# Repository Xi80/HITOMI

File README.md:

# HiT0M1-32

Hardware MIDI Tone Generator Machine - 32

***THIS PROJECT HAS BEEN DISCONTINUED!***

## 仕様

メインMCU:**STM32F303K8 UpTo 72MHz**

PSG音源IC:**YMZ294**

FM音源IC:**YM2413**

最大同時発音数:**PSG6和音,FMメロディー24ch,FMリズム5ch**

入力:**MIDI**

I/F:**USB(UART@9600bps),MIDI(DIN5Pin),3.5mmステレオジャック(出力はモノラル)**

インジケータ:**LEDx1(MIDI IN)**

基板:**100x100,2層**

## ハードウェアについて

回路図を以下に示す。

### Main Board(HiTOMI-32)

### Sub Board(Hikaru)

## ソフトウェア

### 実装した機能

- 30音(メロディー)同時発音可能

- GM1相当の音色マップの一部
- コントロールチェンジ
  - エクスプレッション
  - ボリュームコントロール
- ノートオンイベント
- ノートオフイベント

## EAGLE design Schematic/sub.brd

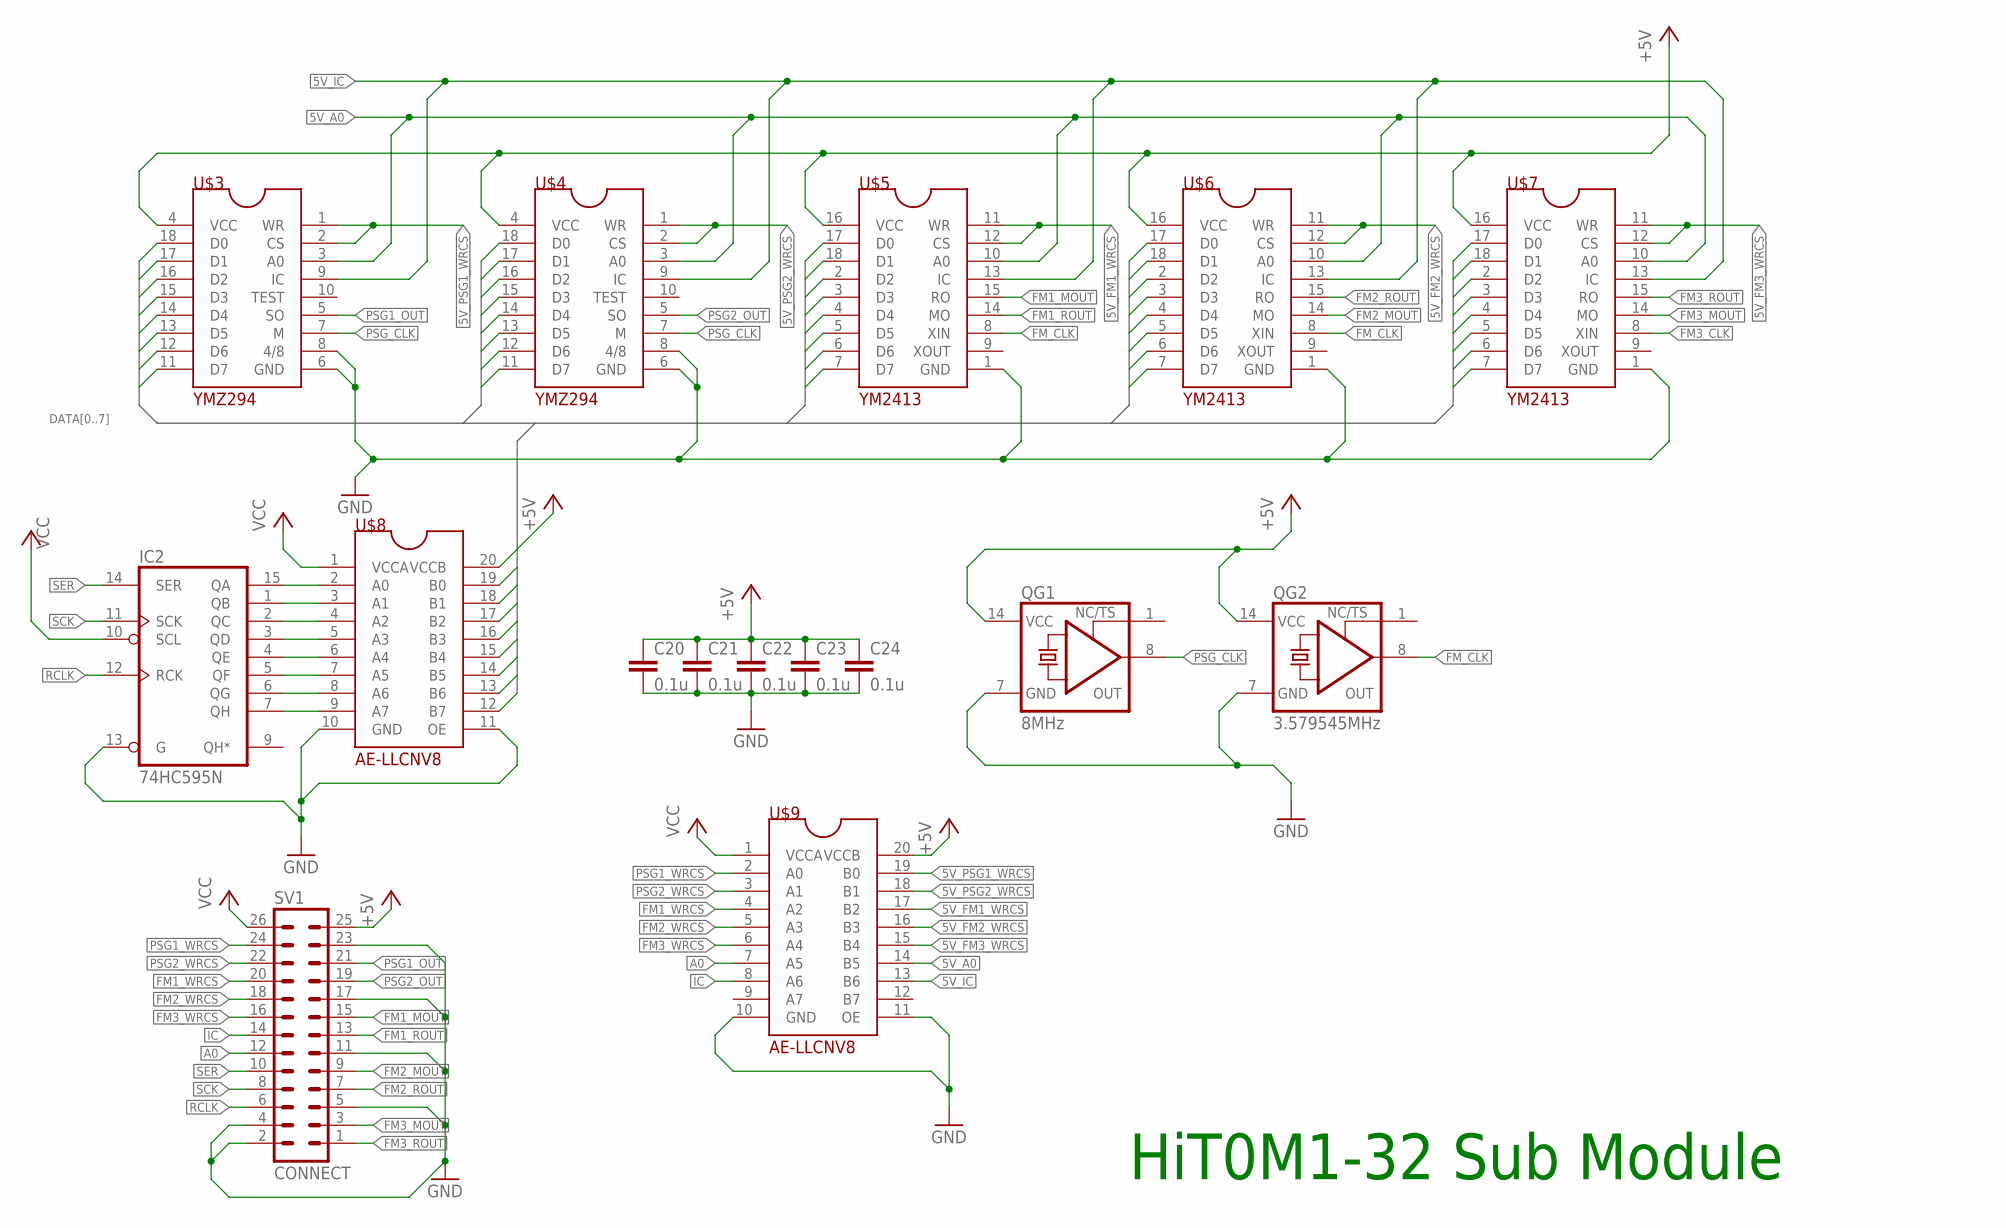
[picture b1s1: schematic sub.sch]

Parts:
C20, C21, C22, C23, C24: 0.1u; C025-025X050
IC2: 74HC595N; DIL16
QG1: 8MHz; DIL14S
QG2: 3.579545MHz; DIL14S
SV1: CONNECT; MA13-2
U$3, U$4: YMZ294; DIL18
U$5, U$6, U$7: YM2413; DIL18
U$8, U$9: AE-LLCNV8; DIL20

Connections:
5V_A0: U$3.3 (A0), U$4.3 (A0), U$5.10 (A0), U$6.10 (A0), U$7.10 (A0), U$9.14 (B5)
5V_FM1_WRCS: U$5.11 (WR), U$5.12 (CS), U$9.17 (B2)
5V_FM2_WRCS: U$6.11 (WR), U$6.12 (CS), U$9.16 (B3)
5V_FM3_WRCS: U$7.11 (WR), U$7.12 (CS), U$9.15 (B4)
5V_IC: U$3.9 (IC), U$4.9 (IC), U$5.13 (IC), U$6.13 (IC), U$7.13 (IC), U$9.13 (B6)
5V_PSG1_WRCS: U$3.1 (WR), U$3.2 (CS), U$9.19 (B0)
5V_PSG2_WRCS: U$4.1 (WR), U$4.2 (CS), U$9.18 (B1)
+5V: C20.1, C21.1, C22.1, C23.1, C24.1, QG1.14 (VCC), QG2.14 (VCC), SV1.25, U$3.4 (VCC), U$4.4 (VCC), U$5.16 (VCC), U$6.16 (VCC), U$7.16 (VCC), U$8.20 (VCCB), U$9.20 (VCCB)
A0: SV1.12, U$9.7 (A5)
DATA0: U$3.18 (D0), U$4.18 (D0), U$5.17 (D0), U$6.17 (D0), U$7.17 (D0), U$8.19 (B0)
DATA1: U$3.17 (D1), U$4.17 (D1), U$5.18 (D1), U$6.18 (D1), U$7.18 (D1), U$8.18 (B1)
DATA2: U$3.16 (D2), U$4.16 (D2), U$5.2 (D2), U$6.2 (D2), U$7.2 (D2), U$8.17 (B2)
DATA3: U$3.15 (D3), U$4.15 (D3), U$5.3 (D3), U$6.3 (D3), U$7.3 (D3), U$8.16 (B3)
DATA4: U$3.14 (D4), U$4.14 (D4), U$5.4 (D4), U$6.4 (D4), U$7.4 (D4), U$8.15 (B4)
DATA5: U$3.13 (D5), U$4.13 (D5), U$5.5 (D5), U$6.5 (D5), U$7.5 (D5), U$8.14 (B5)
DATA6: U$3.12 (D6), U$4.12 (D6), U$5.6 (D6), U$6.6 (D6), U$7.6 (D6), U$8.13 (B6)
DATA7: U$3.11 (D7), U$4.11 (D7), U$5.7 (D7), U$6.7 (D7), U$7.7 (D7), U$8.12 (B7)
FM1_MOUT: SV1.15, U$5.15 (RO)
FM1_ROUT: SV1.13, U$5.14 (MO)
FM1_WRCS: SV1.20, U$9.4 (A2)
FM2_MOUT: SV1.9, U$6.14 (MO)
FM2_ROUT: SV1.7, U$6.15 (RO)
FM2_WRCS: SV1.18, U$9.5 (A3)
FM3_CLK: U$7.8 (XIN)
FM3_MOUT: SV1.3, U$7.14 (MO)
FM3_ROUT: SV1.1, U$7.15 (RO)
FM3_WRCS: SV1.16, U$9.6 (A4)
FM_CLK: QG2.8 (OUT), U$5.8 (XIN), U$6.8 (XIN)
GND: C20.2, C21.2, C22.2, C23.2, C24.2, IC2.8 (GND), IC2.13 (G), QG1.7 (GND), QG2.7 (GND), SV1.2, SV1.4, SV1.5, SV1.11, SV1.17, SV1.23, U$3.6 (GND), U$3.8 (4/8), U$4.6 (GND), U$4.8 (4/8), U$5.1 (GND), U$6.1 (GND), U$7.1 (GND), U$8.10 (GND), U$8.11 (OE), U$9.10 (GND), U$9.11 (OE)
IC: SV1.14, U$9.8 (A6)
unnamed: IC2.15 (QA), U$8.2 (A0)
unnamed: IC2.1 (QB), U$8.3 (A1)
unnamed: IC2.2 (QC), U$8.4 (A2)
unnamed: IC2.4 (QE), U$8.6 (A4)
unnamed: IC2.3 (QD), U$8.5 (A3)
unnamed: IC2.5 (QF), U$8.7 (A5)
unnamed: IC2.6 (QG), U$8.8 (A6)
unnamed: IC2.7 (QH), U$8.9 (A7)
PSG1_OUT: SV1.21, U$3.5 (SO)
PSG1_WRCS: SV1.24, U$9.2 (A0)
PSG2_OUT: SV1.19, U$4.5 (SO)
PSG2_WRCS: SV1.22, U$9.3 (A1)
PSG_CLK: QG1.8 (OUT), U$3.7 (M), U$4.7 (M)
RCLK: IC2.12 (RCK), SV1.6
SCK: IC2.11 (SCK), SV1.8
SER: IC2.14 (SER), SV1.10
VCC: IC2.10 (SCL), IC2.16 (VCC), SV1.26, U$8.1 (VCCA), U$9.1 (VCCA)

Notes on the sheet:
HiT0M1-32 Sub Module

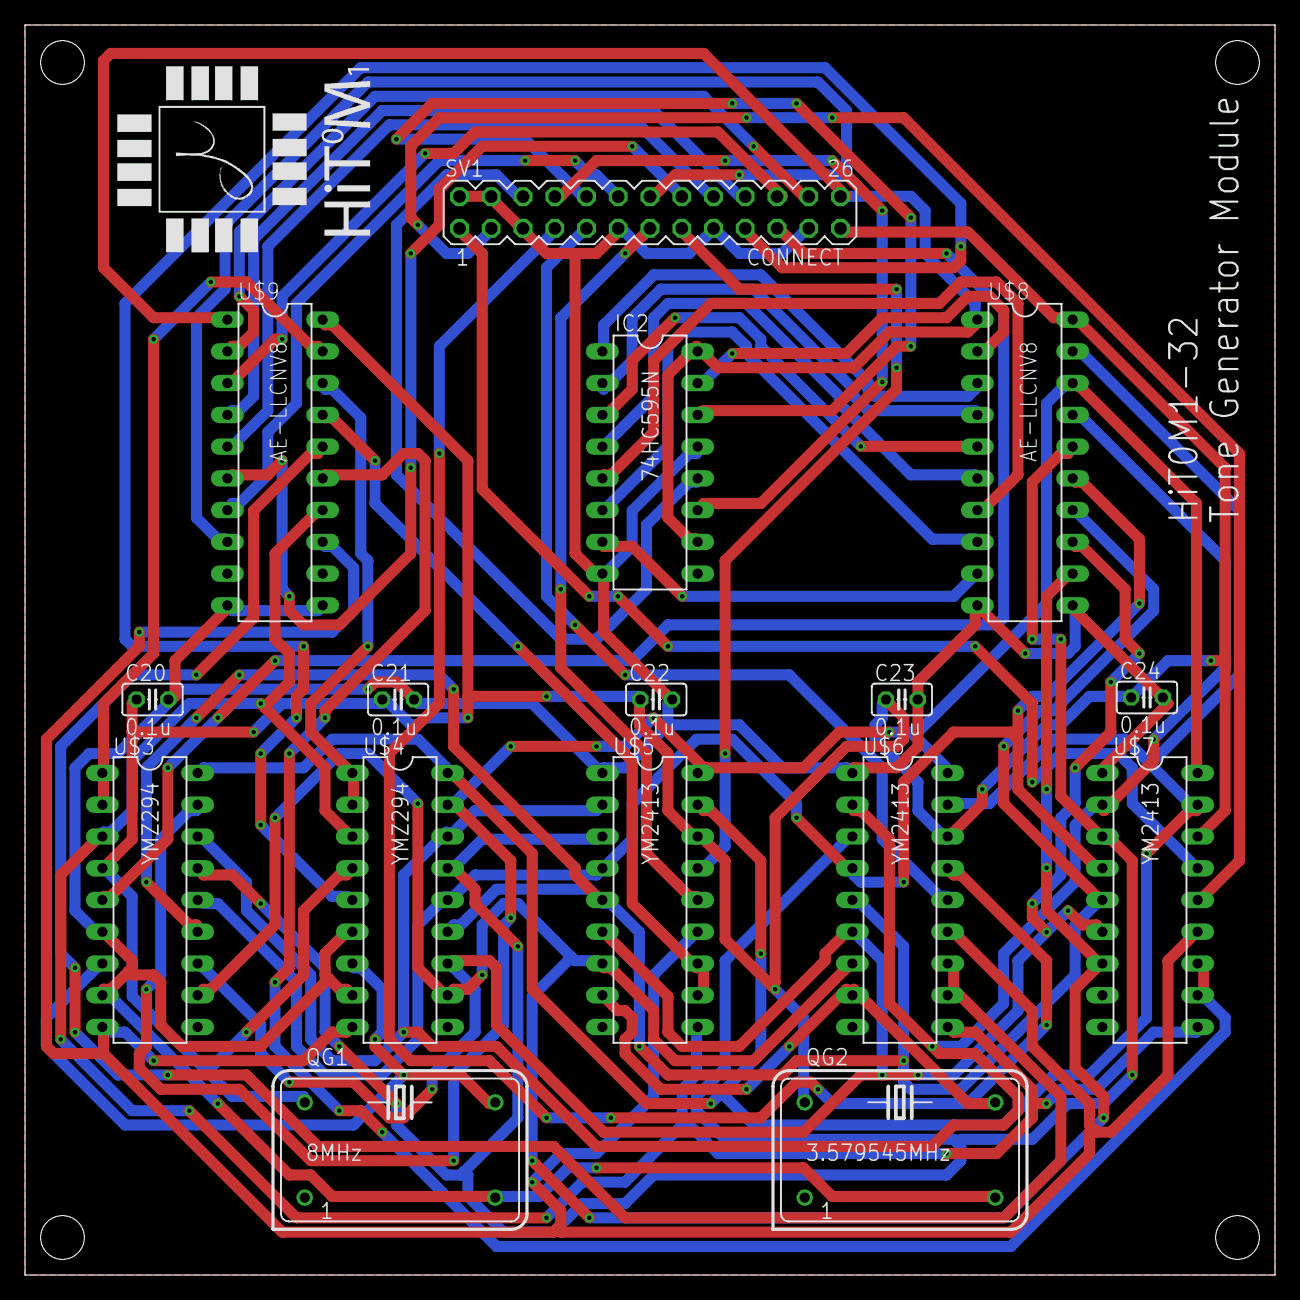
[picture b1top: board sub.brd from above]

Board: 2 copper layers, 100.0 x 100.0 mm, 16 parts (0 on the bottom side), 46 nets.

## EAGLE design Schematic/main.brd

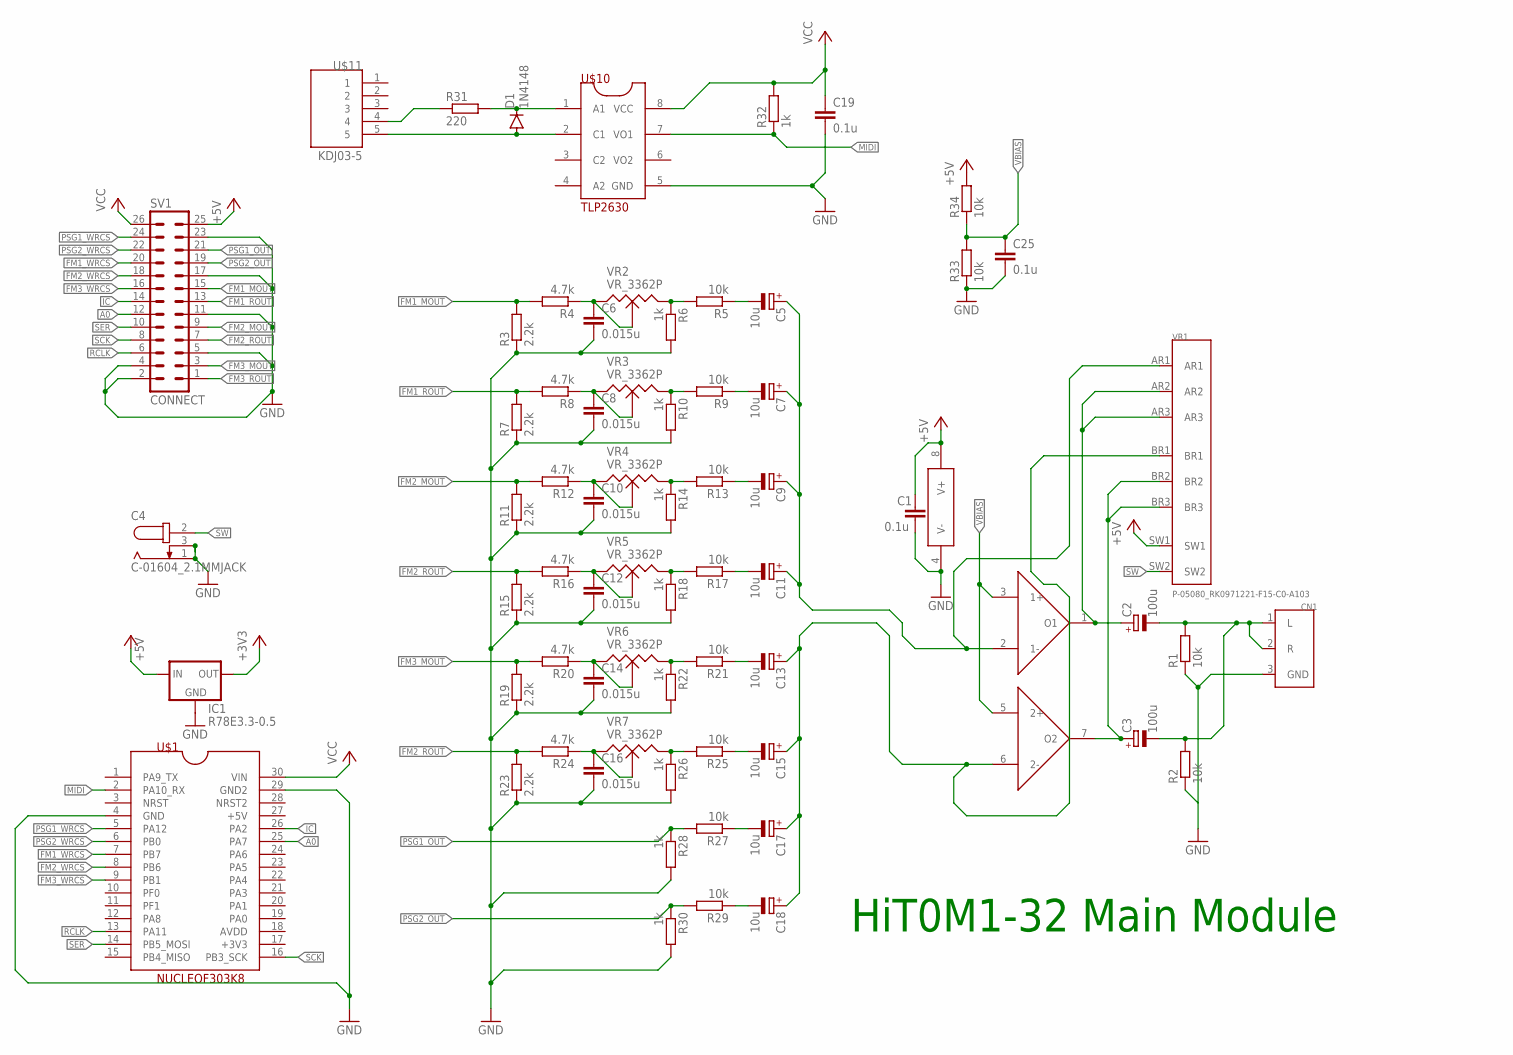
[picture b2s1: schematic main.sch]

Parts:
C1, C19, C25: 0.1u; C025-025X050
C2, C3: 100u; E2,5-6E
C4: C-01604_2.1MMJACK; 2.1MMJACK
C5, C7, C9, C11, C13, C15, C17, C18: 10u; E2,5-6E
C6, C8, C10, C12, C14, C16: 0.015u; C050-025X075
CN1: C-08958_MJ-352W-0; MJ-352W-0
D1: 1N4148; DO35-7
IC1: R78E3.3-0.5; 78XXS
R1, R2, R5, R9, R13, R17, R21, R25, R27, R29, R33, R34: 10k; 0204/7
R3, R7, R11, R15, R19, R23: 2.2k; 0204/7
R4, R8, R12, R16, R20, R24: 4.7k; 0204/7
R6, R10, R14, R18, R22, R26, R28, R30, R32: 1k; 0204/7
R31: 220; 0204/7
SV1: CONNECT; MA13-2
U$1: NUCLEOF303K8
U$2: NJM2114; DIL08
U$10: TLP2630; DIL08
U$11: KDJ03-5
VR1: P-05080_RK0971221-F15-C0-A103; RK0971221-F15-C0-A103
VR2, VR3, VR4, VR5, VR6, VR7: VR_3362P

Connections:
+3V3: IC1.OUT
+5V: C1.1, IC1.IN, R34.2, SV1.25, U$2.8 (V+), VR1.SW1
A0: SV1.12, U$1.25 (PA7)
FM1_MOUT: R3.2, R4.2, SV1.15
FM1_ROUT: R7.2, R8.2, SV1.13
FM1_WRCS: SV1.20, U$1.7 (PB7)
FM2_MOUT: R11.2, R12.2, SV1.9
FM2_ROUT: R15.2, R16.2, R23.2, R24.2, SV1.7
FM2_WRCS: SV1.18, U$1.8 (PB6)
FM3_MOUT: R19.2, R20.2, SV1.3
FM3_ROUT: SV1.1
FM3_WRCS: SV1.16, U$1.9 (PB1)
GND: C1.2, C4.1 (GND), C4.3 (S), C6.2, C8.2, C10.2, C12.2, C14.2, C16.2, C19.2, C25.2, CN1.3 (GND), IC1.GND, R1.1, R3.1, R6.2, R7.1, R10.2, R11.1, R14.2, R15.1, R18.2, R19.1, R22.2, R23.1, R26.2, R28.2, R30.2, R33.1, SV1.2, SV1.4, SV1.5, SV1.11, SV1.17, SV1.23, U$1.4 (GND), U$1.29 (GND2), U$2.4 (V-), U$10.5 (GND)
IC: SV1.14, U$1.26 (PA2)
MIDI: R32.1, U$1.2 (PA10_RX), U$10.7 (VO1)
MIX_1: C5.+, C7.+, C9.+, C11.+, U$2.2 (1-), VR1.AR1
MIX_2: C13.+, C15.+, C17.+, C18.+, U$2.6 (2-), VR1.BR1
unnamed: D1.C, R31.2, U$10.1 (A1)
unnamed: C2.+, U$2.1 (O1), VR1.AR2, VR1.AR3
unnamed: C3.+, U$2.7 (O2), VR1.BR2, VR1.BR3
unnamed: C8.1, R8.1, VR3.1, VR3.2
unnamed: D1.A, U$10.2 (C1), U$11.5
unnamed: C6.1, R4.1, VR2.1, VR2.2
unnamed: R5.2, R6.1, VR2.3
unnamed: C5.-, R5.1
unnamed: R9.2, R10.1, VR3.3
unnamed: C7.-, R9.1
unnamed: C10.1, R12.1, VR4.1, VR4.2
unnamed: R13.2, R14.1, VR4.3
unnamed: C9.-, R13.1
unnamed: C12.1, R16.1, VR5.1, VR5.2
unnamed: R17.2, R18.1, VR5.3
unnamed: C11.-, R17.1
unnamed: C14.1, R20.1, VR6.1, VR6.2
unnamed: R21.2, R22.1, VR6.3
unnamed: C13.-, R21.1
unnamed: C16.1, R24.1, VR7.1, VR7.2
unnamed: R25.2, R26.1, VR7.3
unnamed: C15.-, R25.1
unnamed: C17.-, R27.1
unnamed: C18.-, R29.1
unnamed: R31.1, U$11.4
OUT: C2.-, C3.-, CN1.1 (L), CN1.2 (R), R1.2, R2.2
PSG1_OUT: R27.2, R28.1, SV1.21
PSG1_WRCS: SV1.24, U$1.5 (PA12)
PSG2_OUT: R29.2, R30.1, SV1.19
PSG2_WRCS: SV1.22, U$1.6 (PB0)
RCLK: SV1.6, U$1.13 (PA11)
SCK: SV1.8, U$1.16 (PB3_SCK)
SER: SV1.10, U$1.14 (PB5_MOSI)
SW: C4.2 (VCC), VR1.SW2
VBIAS: C25.1, R33.2, R34.1, U$2.3 (1+), U$2.5 (2+)
VCC: C19.1, R32.2, SV1.26, U$1.30 (VIN), U$10.8 (VCC)

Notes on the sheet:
HiT0M1-32 Main Module

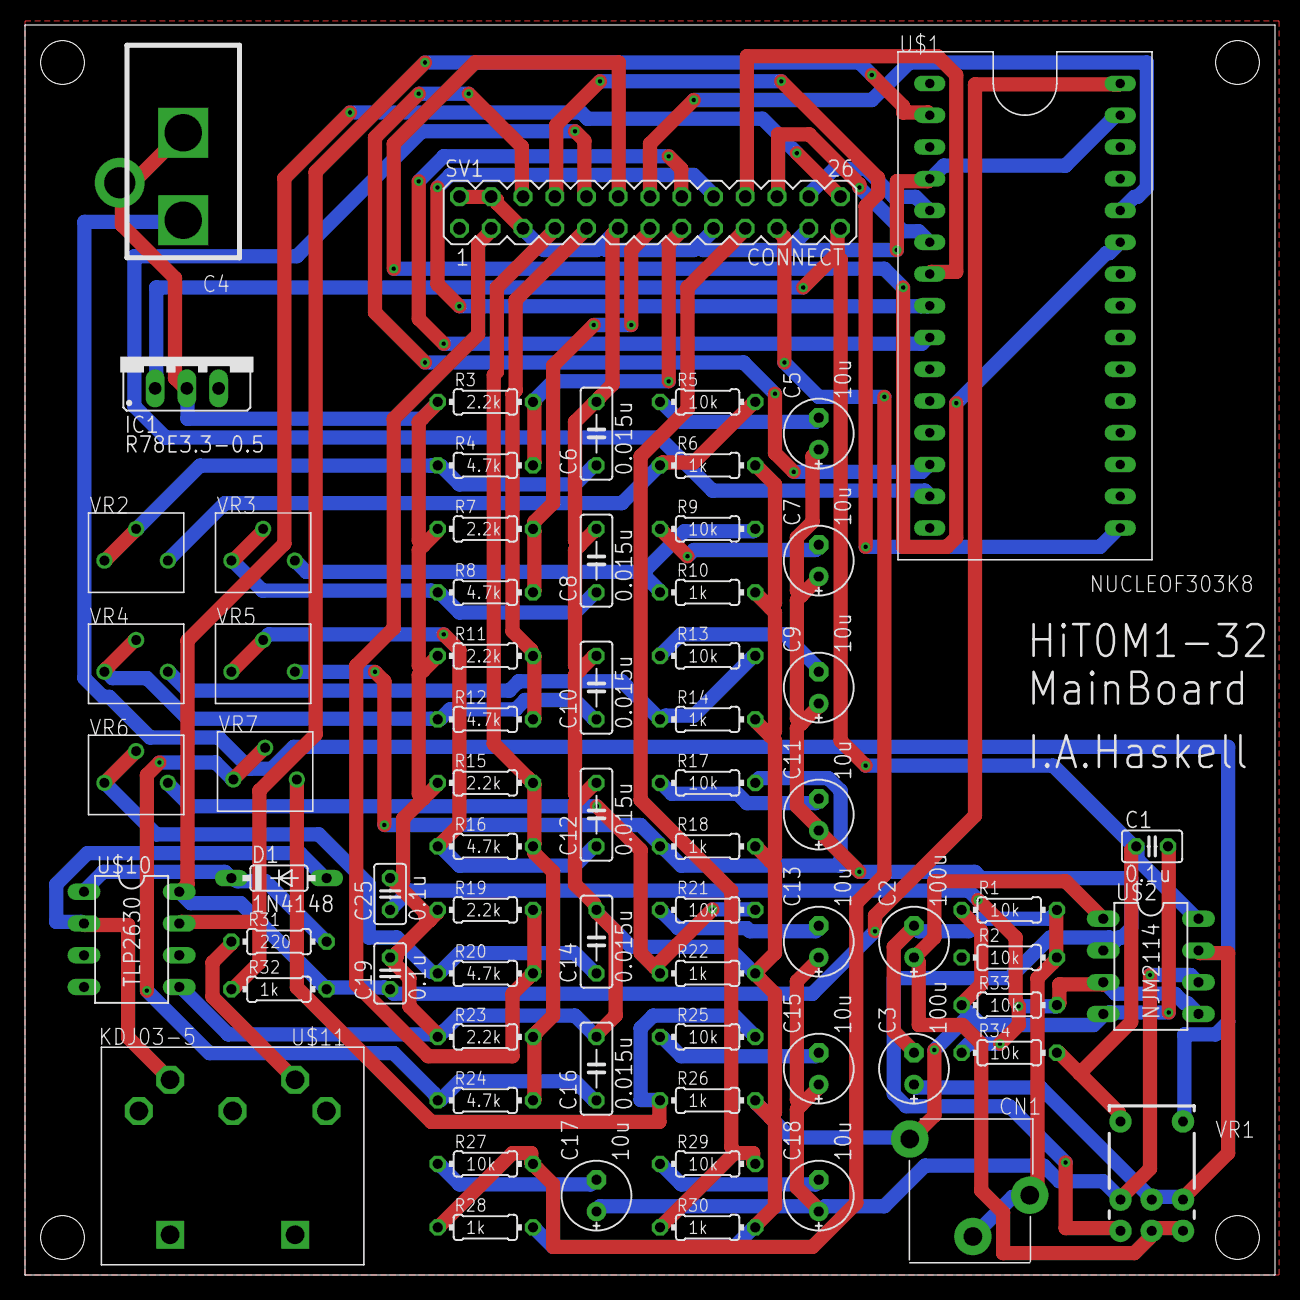
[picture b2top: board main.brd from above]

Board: 2 copper layers, 100.0 x 100.0 mm, 69 parts (0 on the bottom side), 51 nets.

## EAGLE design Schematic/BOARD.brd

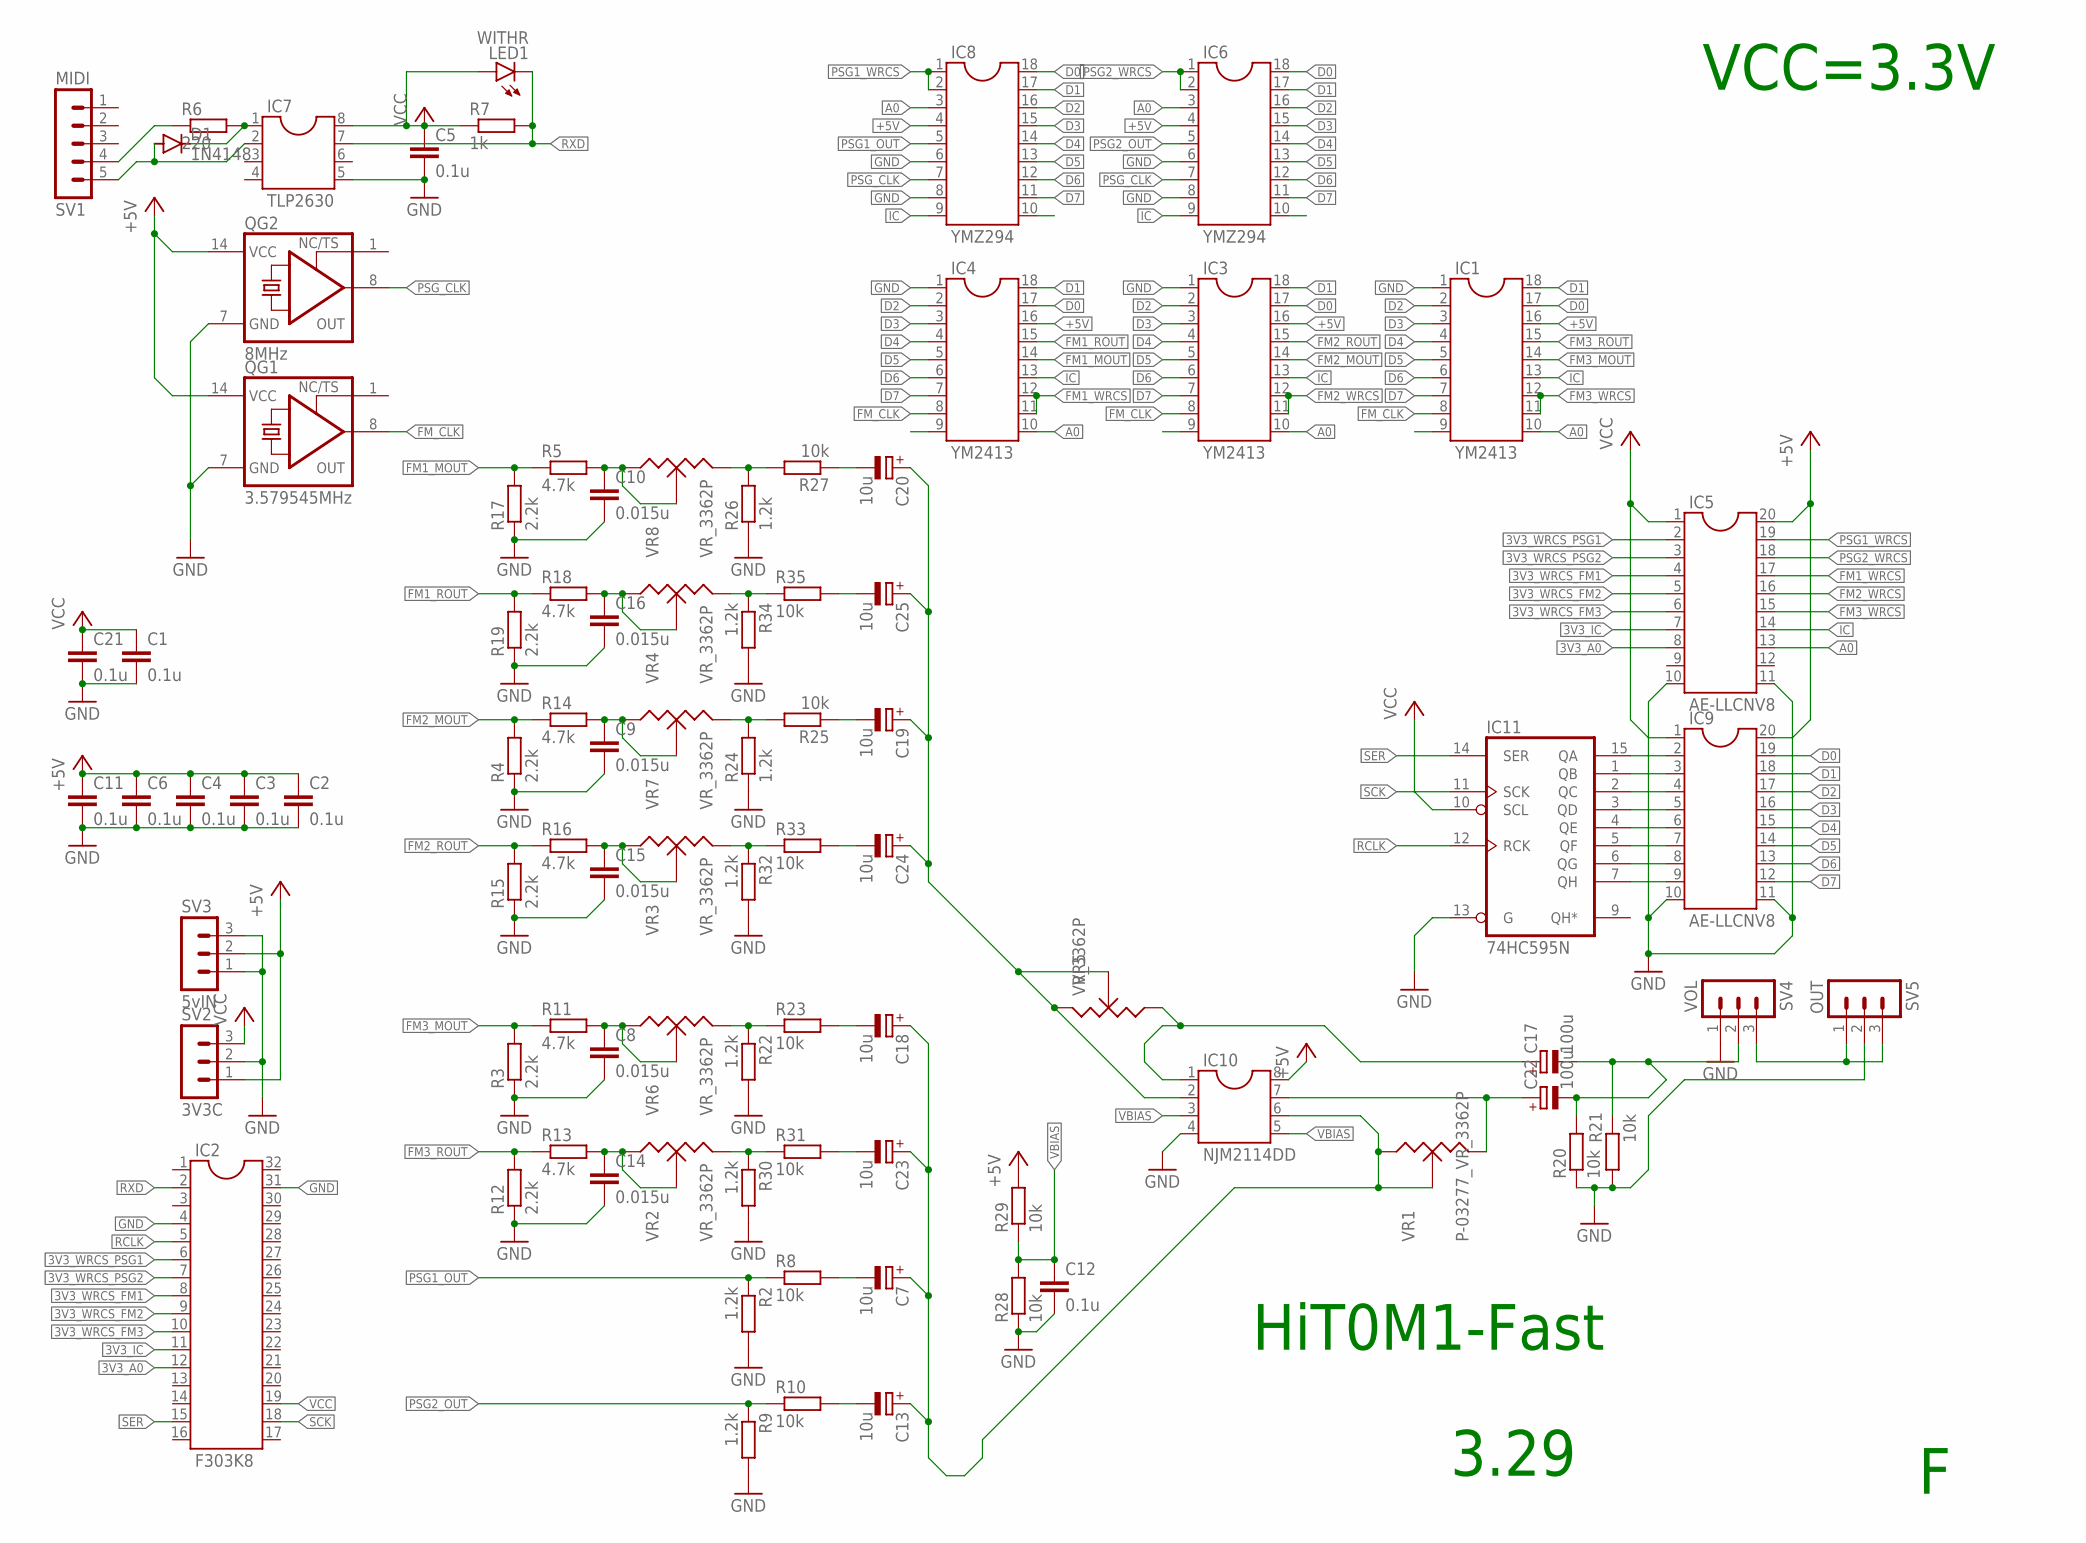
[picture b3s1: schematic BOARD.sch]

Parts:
C1, C2, C3, C4, C5, C6, C11, C12, C21: 0.1u; C025-025X050
C7, C13, C18, C19, C20, C23, C24, C25: 10u; E2,5-6E
C8, C9, C10, C14, C15, C16: 0.015u; C050-025X075
C17, C22: 100u; E2,5-6E
D1: 1N4148; DO35-7
IC1, IC3, IC4: YM2413; SOCKET-18
IC2: F303K8; DIL32
IC5, IC9: AE-LLCNV8; SOCKET-20
IC6, IC8: YMZ294; SOCKET-18
IC7: TLP2630; SOCKET-08
IC10: NJM2114DD; SOCKET-08
IC11: 74HC595N; DIL16
LED1: WITHR; LED3MM
QG1: 3.579545MHz; DIL14S
QG2: 8MHz; DIL14S
R2, R9, R22, R24, R26, R30, R32, R34: 1.2k; 0207/2V
R3, R4, R12, R15, R17, R19: 2.2k; 0207/2V
R5, R11, R13, R14, R16, R18: 4.7k; 0207/2V
R6: 220; 0207/2V
R7: 1k; 0207/2V
R8, R10, R20, R21, R23, R25, R27, R28, R29, R31, R33, R35: 10k; 0207/2V
SV1: MIDI; MA05-1
SV2: 3V3C; MA03-1
SV3: 5vIN; MA03-1
SV4: VOL; MA03-1
SV5: OUT; MA03-1
VR1: P-03277_VR_3362P; VR_3362P
VR2, VR3, VR4, VR5, VR6, VR7, VR8: VR_3362P

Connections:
3V3_A0: IC2.12, IC5.8
3V3_IC: IC2.11, IC5.7
3V3_WRCS_FM1: IC2.8, IC5.4
3V3_WRCS_FM2: IC2.9, IC5.5
3V3_WRCS_FM3: IC2.10, IC5.6
3V3_WRCS_PSG1: IC2.6, IC5.2
3V3_WRCS_PSG2: IC2.7, IC5.3
+5V: C2.1, C3.1, C4.1, C6.1, C11.1, IC1.16, IC3.16, IC4.16, IC5.20, IC6.4, IC8.4, IC9.20, IC10.8, QG1.14 (VCC), QG2.14 (VCC), R29.2, SV2.1, SV3.2
A0: IC1.10, IC3.10, IC4.10, IC5.13, IC6.3, IC8.3
D0: IC1.17, IC3.17, IC4.17, IC6.18, IC8.18, IC9.19
D1: IC1.18, IC3.18, IC4.18, IC6.17, IC8.17, IC9.18
D2: IC1.2, IC3.2, IC4.2, IC6.16, IC8.16, IC9.17
D3: IC1.3, IC3.3, IC4.3, IC6.15, IC8.15, IC9.16
D4: IC1.4, IC3.4, IC4.4, IC6.14, IC8.14, IC9.15
D5: IC1.5, IC3.5, IC4.5, IC6.13, IC8.13, IC9.14
D6: IC1.6, IC3.6, IC4.6, IC6.12, IC8.12, IC9.13
D7: IC1.7, IC3.7, IC4.7, IC6.11, IC8.11, IC9.12
FM1_MOUT: IC4.14, R5.1, R17.2
FM1_ROUT: IC4.15, R18.1, R19.2
FM1_WRCS: IC4.11, IC4.12, IC5.17
FM2_MOUT: IC3.14, R4.2, R14.1
FM2_ROUT: IC3.15, R15.2, R16.1
FM2_WRCS: IC3.11, IC3.12, IC5.16
FM3_MOUT: IC1.14, R3.2, R11.1
FM3_ROUT: IC1.15, R12.2, R13.1
FM3_WRCS: IC1.11, IC1.12, IC5.15
FM_CLK: IC1.8, IC3.8, IC4.8, QG1.8 (OUT)
GND: C1.2, C2.2, C3.2, C4.2, C5.2, C6.2, C8.2, C9.2, C10.2, C11.2, C12.2, C14.2, C15.2, C16.2, C21.2, IC1.1, IC2.4, IC2.31, IC3.1, IC4.1, IC5.10, IC5.11, IC6.6, IC6.8, IC7.5, IC8.6, IC8.8, IC9.10, IC9.11, IC10.4, IC11.8 (GND), IC11.13 (G), QG1.7 (GND), QG2.7 (GND), R2.2, R3.1, R4.1, R9.2, R12.1, R15.1, R17.1, R19.1, R20.1, R21.1, R22.2, R24.1, R26.1, R28.1, R30.2, R32.2, R34.2, SV2.2, SV3.1, SV3.3, SV4.1, SV5.2
IC: IC1.13, IC3.13, IC4.13, IC5.14, IC6.9, IC8.9
unnamed: C10.1, R5.2, VR8.1, VR8.2
unnamed: D1.C, IC7.1, R6.2
unnamed: C16.1, R18.2, VR4.1, VR4.2
unnamed: R6.1, SV1.4
unnamed: IC9.2, IC11.15 (QA)
unnamed: IC9.3, IC11.1 (QB)
unnamed: IC9.4, IC11.2 (QC)
unnamed: IC9.5, IC11.3 (QD)
unnamed: IC9.6, IC11.4 (QE)
unnamed: IC9.7, IC11.5 (QF)
unnamed: IC9.8, IC11.6 (QG)
unnamed: IC9.9, IC11.7 (QH)
unnamed: C9.1, R14.2, VR7.1, VR7.2
unnamed: D1.A, IC7.2, SV1.5
unnamed: C15.1, R16.2, VR3.1, VR3.2
unnamed: C7.+, C13.+, C18.+, C23.+, IC10.6, VR1.1, VR1.2
unnamed: R32.1, R33.1, VR3.3
unnamed: R24.2, R25.2, VR7.3
unnamed: R34.1, R35.1, VR4.3
unnamed: R26.2, R27.2, VR8.3
unnamed: C20.-, R27.1
unnamed: C25.-, R35.2
unnamed: C19.-, R25.1
unnamed: C24.-, R33.2
unnamed: C19.+, C20.+, C24.+, C25.+, IC10.2, VR5.2, VR5.3
unnamed: C8.1, R11.2, VR6.1, VR6.2
unnamed: R22.1, R23.1, VR6.3
unnamed: C18.-, R23.2
unnamed: C14.1, R13.2, VR2.1, VR2.2
unnamed: R30.1, R31.1, VR2.3
unnamed: C23.-, R31.2
unnamed: C7.-, R8.2
unnamed: C13.-, R10.2
unnamed: SV4.3, SV5.1, SV5.3
unnamed: C17.+, IC10.1, VR5.1
unnamed: C22.+, IC10.7, VR1.3
OUT: C17.-, C22.-, R20.2, R21.2, SV4.2
PSG1_OUT: IC8.5, R2.1, R8.1
PSG1_WRCS: IC5.19, IC8.1, IC8.2
PSG2_OUT: IC6.5, R9.1, R10.1
PSG2_WRCS: IC5.18, IC6.1, IC6.2
PSG_CLK: IC6.7, IC8.7, QG2.8 (OUT)
RCLK: IC2.5, IC11.12 (RCK)
RXD: IC2.2, IC7.7, LED1.K (C), R7.2
SCK: IC2.18, IC11.11 (SCK)
SER: IC2.15, IC11.14 (SER)
VBIAS: C12.1, IC10.3, IC10.5, R28.2, R29.1
VCC: C1.1, C5.1, C21.1, IC2.19, IC5.1, IC7.8, IC9.1, IC11.10 (SCL), IC11.16 (VCC), LED1.A, R7.1, SV2.3

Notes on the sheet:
HiT0M1-Fast
VCC=3.3V
3.29

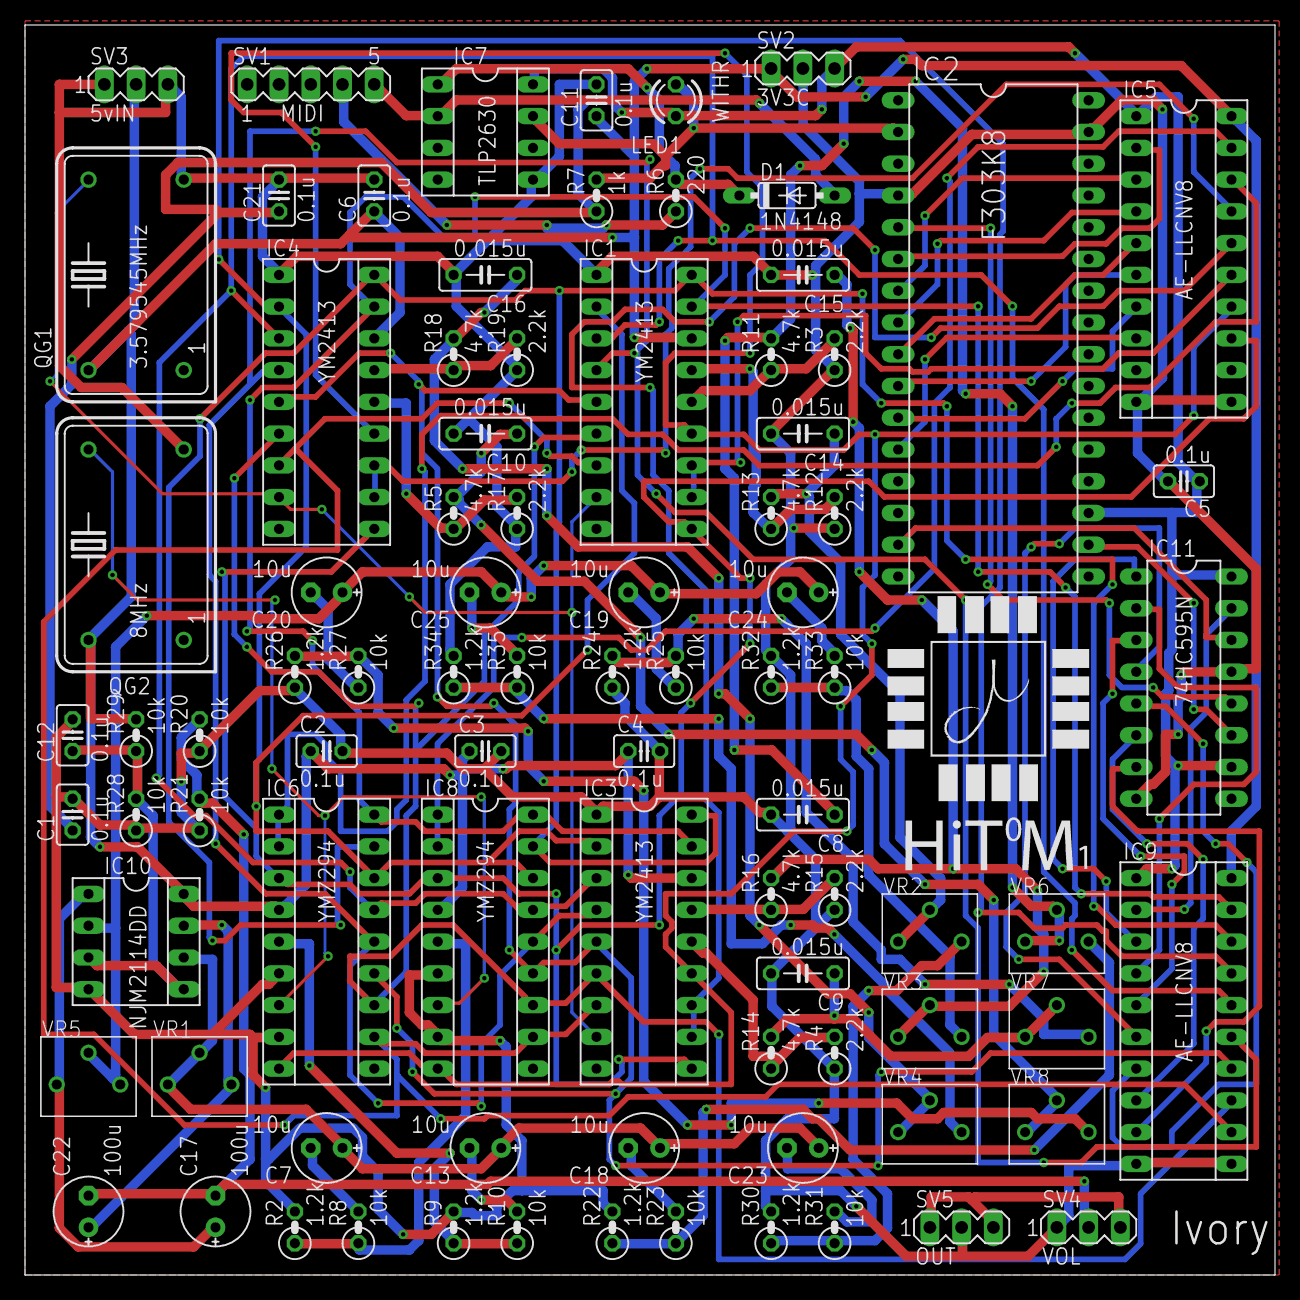
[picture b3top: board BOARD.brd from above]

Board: 2 copper layers, 100.0 x 100.0 mm, 87 parts (0 on the bottom side), 77 nets.

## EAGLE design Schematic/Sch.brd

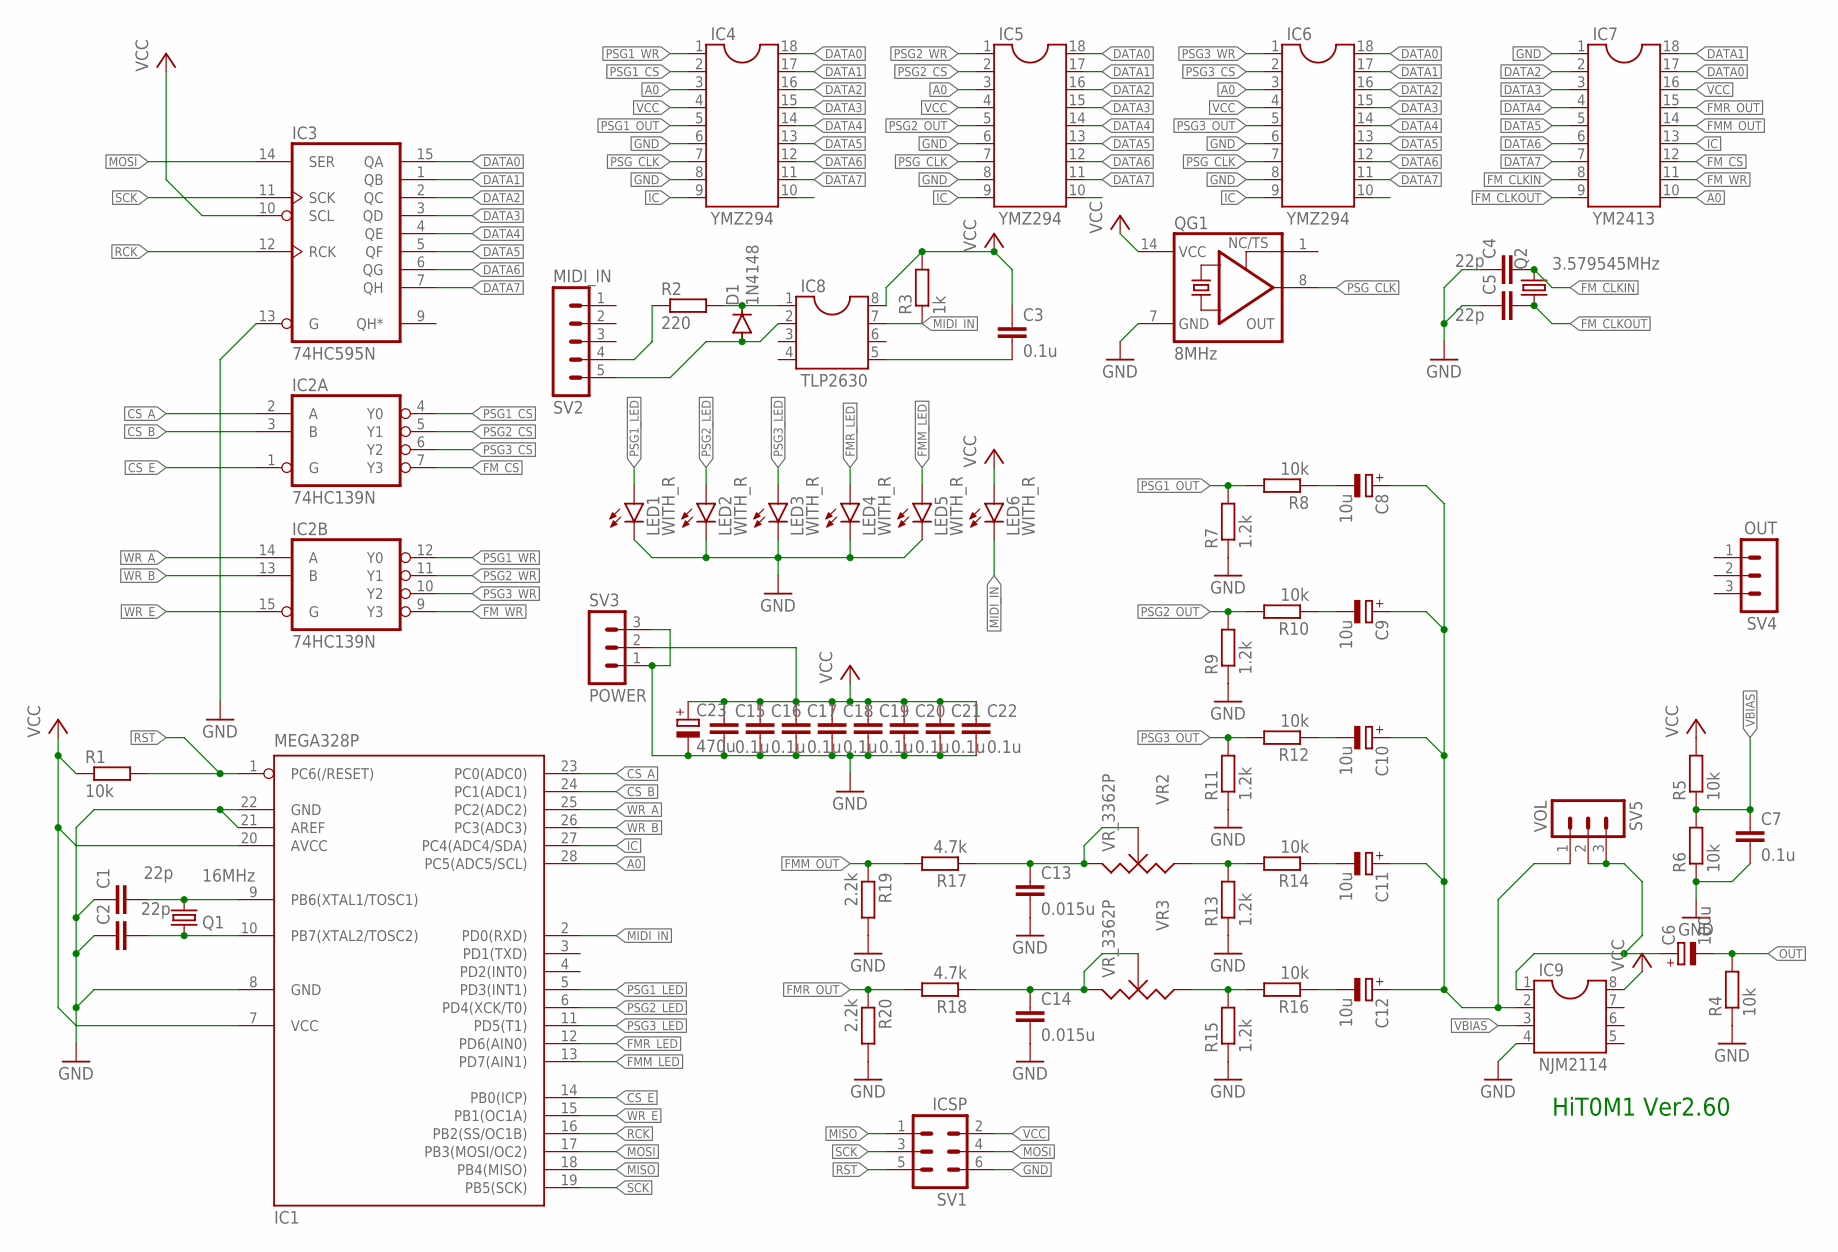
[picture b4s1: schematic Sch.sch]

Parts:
C1, C2, C4, C5: 22p; C025-025X050
C3, C7, C15, C16, C17, C18, C19, C20, C21, C22: 0.1u; C025-025X050
C6: 100u; E2,5-6
C8, C9, C10, C11, C12: 10u; E2,5-6
C13, C14: 0.015u; C050-025X075
C23: 470u; E2,5-6
D1: 1N4148; DO35-7
IC1: MEGA328P; DIL28-3
IC2: 74HC139N; DIL16
IC3: 74HC595N; DIL16
IC4, IC5, IC6: YMZ294; SOCKET-18
IC7: YM2413; SOCKET-18
IC8: TLP2630; SOCKET-08
IC9: NJM2114; SOCKET-08
LED1, LED2, LED3, LED4, LED5, LED6: WITH_R; LED3MM
Q1: 16MHz; HC49/S
Q2: 3.579545MHz; HC49/S
QG1: 8MHz; DIL14S
R1, R4, R5, R6: 10k; 0207/10
R2: 220; 0207/10
R3: 1k; 0207/10
R7, R9, R11, R13, R15: 1.2k; 0207/2V
R8, R10, R12, R14, R16: 10k; 0207/2V
R17, R18: 4.7k; 0207/2V
R19, R20: 2.2k; 0207/2V
SV1: ICSP; MA03-2
SV2: MIDI_IN; MA05-1
SV3: POWER; MA03-1
SV4: OUT; MA03-1
SV5: VOL; MA03-1
VR2, VR3: VR_3362P

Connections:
A0: IC1.28 (PC5(ADC5/SCL)), IC4.3, IC5.3, IC6.3, IC7.10
CS_A: IC1.23 (PC0(ADC0)), IC2.2 (A)
CS_B: IC1.24 (PC1(ADC1)), IC2.3 (B)
CS_E: IC1.14 (PB0(ICP)), IC2.1 (G)
DATA0: IC3.15 (QA), IC4.18, IC5.18, IC6.18, IC7.17
DATA1: IC3.1 (QB), IC4.17, IC5.17, IC6.17, IC7.18
DATA2: IC3.2 (QC), IC4.16, IC5.16, IC6.16, IC7.2
DATA3: IC3.3 (QD), IC4.15, IC5.15, IC6.15, IC7.3
DATA4: IC3.4 (QE), IC4.14, IC5.14, IC6.14, IC7.4
DATA5: IC3.5 (QF), IC4.13, IC5.13, IC6.13, IC7.5
DATA6: IC3.6 (QG), IC4.12, IC5.12, IC6.12, IC7.6
DATA7: IC3.7 (QH), IC4.11, IC5.11, IC6.11, IC7.7
FMM_LED: IC1.13 (PD7(AIN1)), LED5.A
FMM_OUT: IC7.14, R17.2, R19.1
FMR_LED: IC1.12 (PD6(AIN0)), LED4.A
FMR_OUT: IC7.15, R18.2, R20.1
FM_CLKIN: C4.2, IC7.8, Q2.2
FM_CLKOUT: C5.2, IC7.9, Q2.1
FM_CS: IC2.7 (Y3), IC7.12
FM_WR: IC2.9 (Y3), IC7.11
GND: C1.1, C2.1, C4.1, C5.1, C7.2, C13.2, C14.2, C15.2, C16.2, C17.2, C18.2, C19.2, C20.2, C21.2, C22.2, C23.-, IC1.8 (GND), IC1.21 (AREF), IC1.22 (GND), IC2.8 (GND), IC3.8 (GND), IC3.13 (G), IC4.6, IC4.8, IC5.6, IC5.8, IC6.6, IC6.8, IC7.1, IC9.4, LED1.K (C), LED2.K (C), LED3.K (C), LED4.K (C), LED5.K (C), QG1.7 (GND), R4.1, R6.1, R7.1, R9.1, R11.1, R13.1, R15.1, R19.2, R20.2, SV1.6, SV3.1, SV3.3
IC: IC1.27 (PC4(ADC4/SDA)), IC4.9, IC5.9, IC6.9, IC7.13
MIDI_IN: IC1.2 (PD0(RXD)), IC8.7, LED6.K (C), R3.1
MISO: IC1.18 (PB4(MISO)), SV1.1
MOSI: IC1.17 (PB3(MOSI/OC2)), IC3.14 (SER), SV1.4
unnamed: C1.2, IC1.9 (PB6(XTAL1/TOSC1)), Q1.2
unnamed: R2.1, SV2.4
unnamed: D1.C, IC8.1, R2.2
unnamed: D1.A, IC8.2, SV2.5
unnamed: C3.2, IC8.5
unnamed: C6.+, IC9.1, SV5.2, SV5.3
unnamed: C8.-, R8.1
unnamed: C2.2, IC1.10 (PB7(XTAL2/TOSC2)), Q1.1
unnamed: C9.-, R10.1
unnamed: C10.-, R12.1
unnamed: R13.2, R14.2, VR2.1
unnamed: C11.-, R14.1
unnamed: R15.2, R16.2, VR3.1
unnamed: C12.-, R16.1
unnamed: C14.1, R18.1, VR3.2, VR3.3
unnamed: C8.+, C9.+, C10.+, C11.+, C12.+, IC9.2, SV5.1
unnamed: C13.1, R17.1, VR2.2, VR2.3
OUT: C6.-, R4.2
PSG1_CS: IC2.4 (Y0), IC4.2
PSG1_LED: IC1.5 (PD3(INT1)), LED1.A
PSG1_OUT: IC4.5, R7.2, R8.2
PSG1_WR: IC2.12 (Y0), IC4.1
PSG2_CS: IC2.5 (Y1), IC5.2
PSG2_LED: IC1.6 (PD4(XCK/T0)), LED2.A
PSG2_OUT: IC5.5, R9.2, R10.2
PSG2_WR: IC2.11 (Y1), IC5.1
PSG3_CS: IC2.6 (Y2), IC6.2
PSG3_LED: IC1.11 (PD5(T1)), LED3.A
PSG3_OUT: IC6.5, R11.2, R12.2
PSG3_WR: IC2.10 (Y2), IC6.1
PSG_CLK: IC4.7, IC5.7, IC6.7, QG1.8 (OUT)
RCK: IC1.16 (PB2(SS/OC1B)), IC3.12 (RCK)
RST: IC1.1 (PC6(/RESET)), R1.2, SV1.5
SCK: IC1.19 (PB5(SCK)), IC3.11 (SCK), SV1.3
VBIAS: C7.1, IC9.3, R5.1, R6.2
VCC: C3.1, C15.1, C16.1, C17.1, C18.1, C19.1, C20.1, C21.1, C22.1, C23.+, IC1.7 (VCC), IC1.20 (AVCC), IC2.16 (VCC), IC3.10 (SCL), IC3.16 (VCC), IC4.4, IC5.4, IC6.4, IC7.16, IC8.8, IC9.8, LED6.A, QG1.14 (VCC), R1.1, R3.2, R5.2, SV1.2, SV3.2
WR_A: IC1.25 (PC2(ADC2)), IC2.14 (A)
WR_B: IC1.26 (PC3(ADC3)), IC2.13 (B)
WR_E: IC1.15 (PB1(OC1A)), IC2.15 (G)

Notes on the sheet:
HiT0M1 Ver2.60
